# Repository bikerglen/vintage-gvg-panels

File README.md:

# vintage-gvg-panels
# kalypso, series 300

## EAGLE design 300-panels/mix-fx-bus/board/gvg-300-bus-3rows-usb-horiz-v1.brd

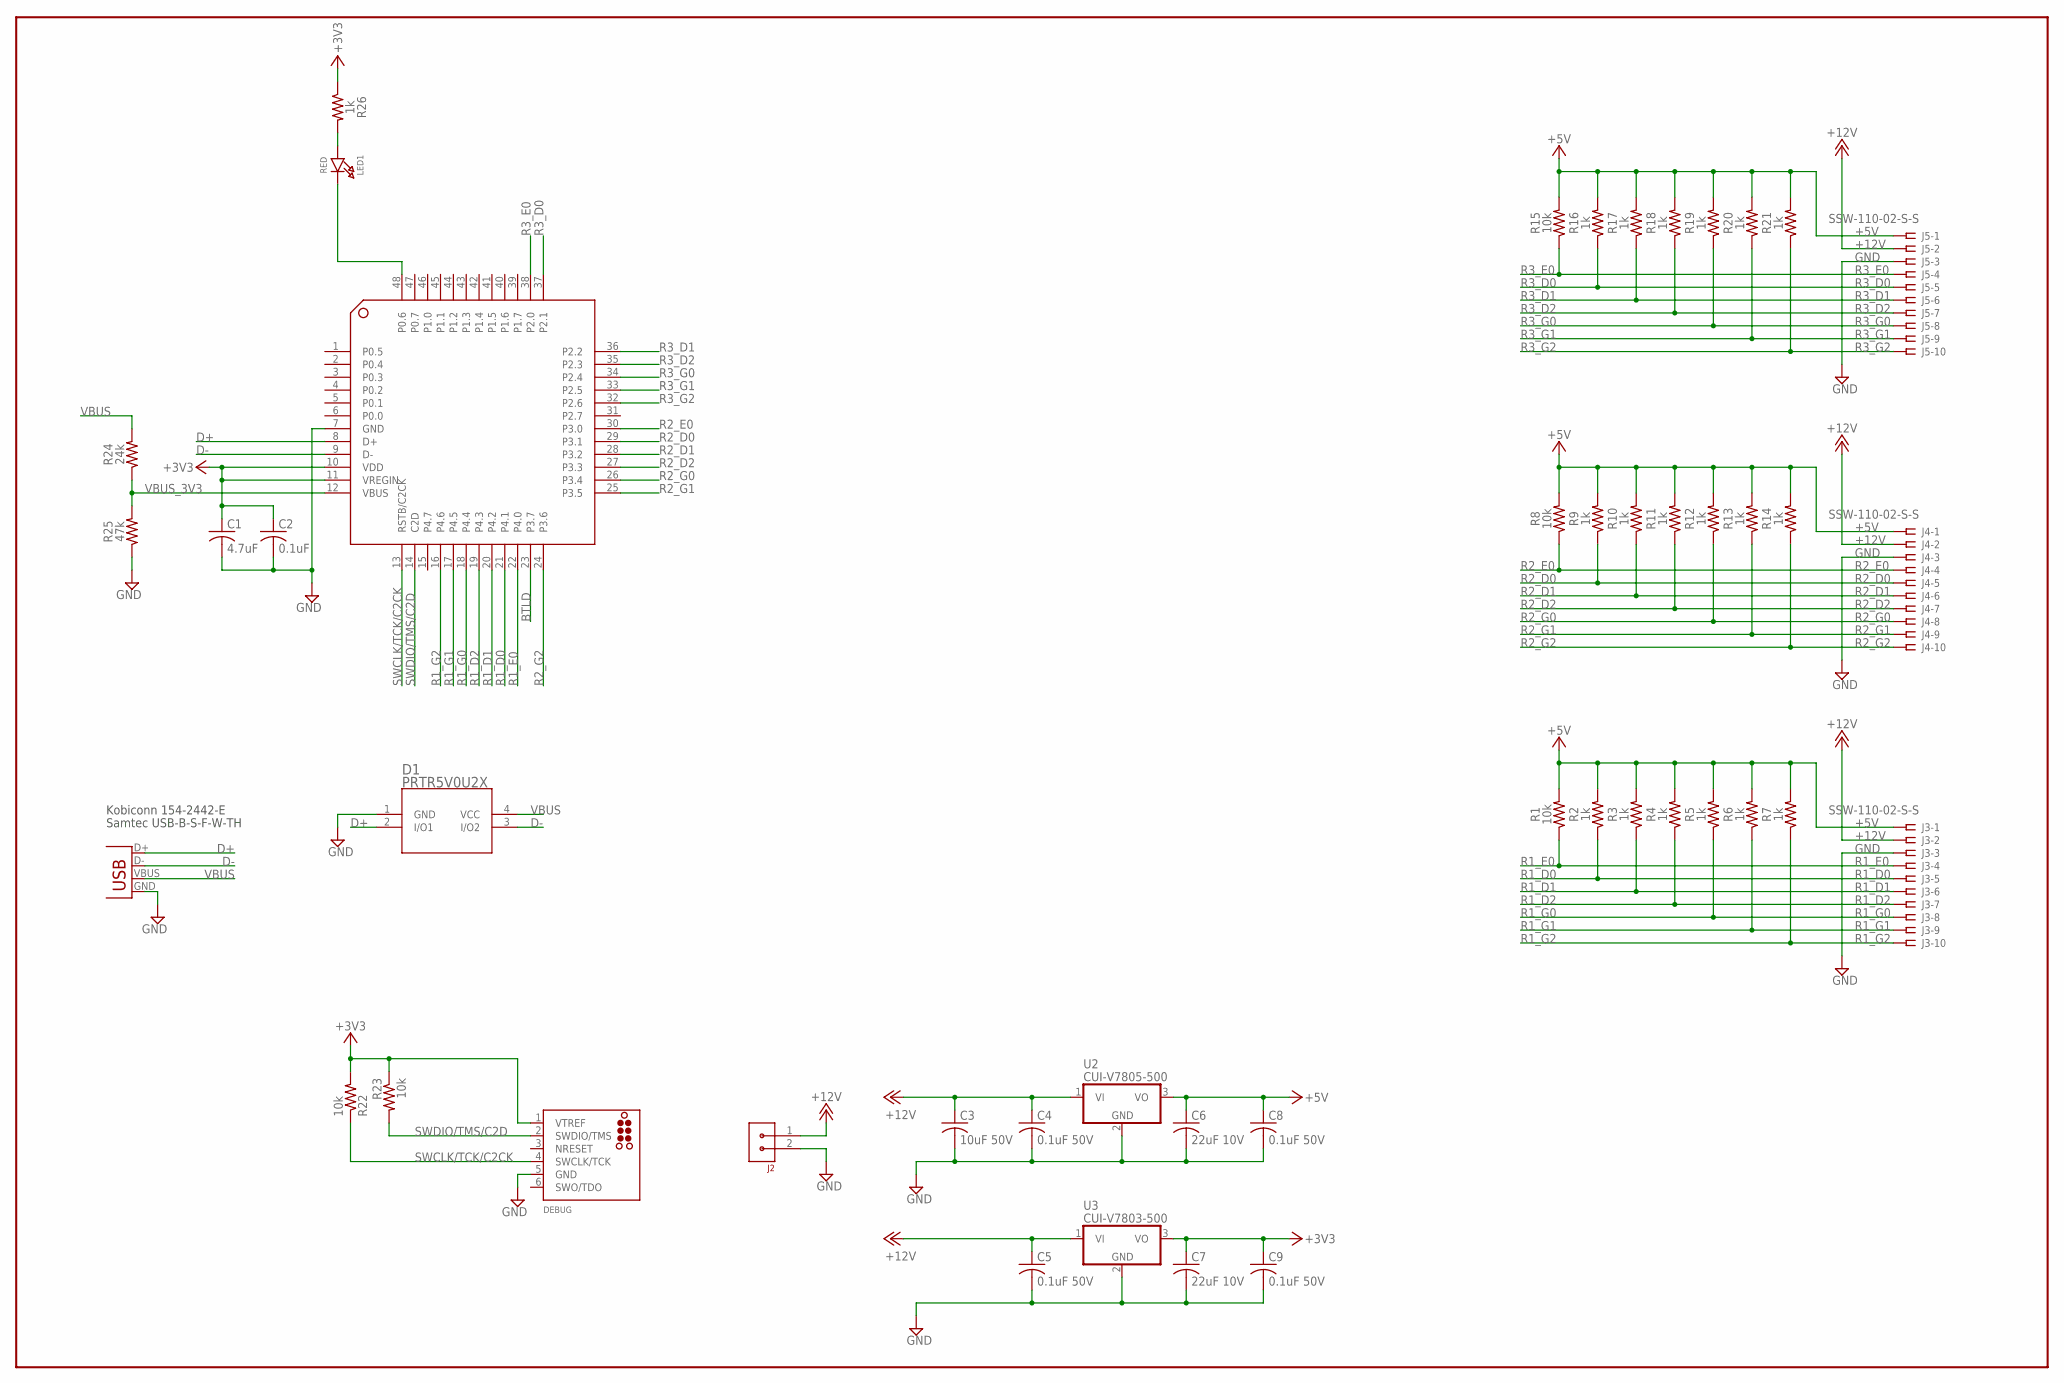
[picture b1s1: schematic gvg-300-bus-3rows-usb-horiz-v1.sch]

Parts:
C1: 4.7uF; C0805K
C2: 0.1uF; C0603K
C3: 10uF 50V; C1210K; MFR_PART_NO C1210C106K5RACTU
C4, C5, C8, C9: 0.1uF 50V; C1206K; MFR_PART_NO C1206S104M5RACTU
C6, C7: 22uF 10V; C1206K; MFR_PART_NO C1206C226K8RAC7800
D1: PRTR5V0U2X; SOT143B
DEBUG: TC2030-CTX-SWD; TC2030-MCP-NL
J1: USB-B; USB-B-PTH; MFR_PART_NO 154-2442-E
J2: CON-3.81MM-1X2-PHOENIX; CON-PHOENIX-3.81-1X2-RA
J3, J4, J5: SSW-110-02-S-S
LED1: RED; CHIPLED_0805_NOOUTLINE
R1, R8, R15, R22, R23: 10k; R0603
R2, R3, R4, R5, R6, R7, R9, R10, R11, R12, R13, R14, R16, R17, R18, R19, R20, R21, R26: 1k; R0603
R24: 24k; R0603
R25: 47k; R0603
U1: EFM8UB20F64G-B-QFP48; EFM8UB2-QFP48
U2: CUI-V7805-500; CUI-78XX-500
U3: CUI-V7803-500; CUI-78XX-500

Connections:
+3V3: C1.1, C2.1, C7.1, C9.1, DEBUG.1 (VTREF), R22.2, R23.1, R26.1, U1.10 (VDD), U1.11 (VREGIN), U3.3 (VO)
+5V: C6.1, C8.1, J3.1, J4.1, J5.1, R1.2, R2.2, R3.2, R4.2, R5.2, R6.2, R7.2, R8.2, R9.2, R10.2, R11.2, R12.2, R13.2, R14.2, R15.2, R16.2, R17.2, R18.2, R19.2, R20.2, R21.2, U2.3 (VO)
+12V: C3.1, C4.1, C5.1, J2.1, J3.2, J4.2, J5.2, U2.1 (VI), U3.1 (VI)
BTLD: U1.23 (P3.7)
D+: D1.2 (I/O1), J1.D+, U1.8 (D+)
D-: D1.3 (I/O2), J1.D-, U1.9 (D-)
GND: C1.2, C2.2, C3.2, C4.2, C5.2, C6.2, C7.2, C8.2, C9.2, D1.1 (GND), DEBUG.5 (GND), J1.GND, J2.2, J3.3, J4.3, J5.3, R25.1, U1.7 (GND), U2.2 (GND), U3.2 (GND)
unnamed: LED1.A, R26.2
unnamed: LED1.C, U1.48 (P0.6)
NRESET: DEBUG.3 (NRESET)
R1_D0: J3.5, R2.1, U1.21 (P4.1)
R1_D1: J3.6, R3.1, U1.20 (P4.2)
R1_D2: J3.7, R4.1, U1.19 (P4.3)
R1_E0: J3.4, R1.1, U1.22 (P4.0)
R1_G0: J3.8, R5.1, U1.18 (P4.4)
R1_G1: J3.9, R6.1, U1.17 (P4.5)
R1_G2: J3.10, R7.1, U1.16 (P4.6)
R2_D0: J4.5, R9.1, U1.29 (P3.1)
R2_D1: J4.6, R10.1, U1.28 (P3.2)
R2_D2: J4.7, R11.1, U1.27 (P3.3)
R2_E0: J4.4, R8.1, U1.30 (P3.0)
R2_G0: J4.8, R12.1, U1.26 (P3.4)
R2_G1: J4.9, R13.1, U1.25 (P3.5)
R2_G2: J4.10, R14.1, U1.24 (P3.6)
R3_D0: J5.5, R16.1, U1.37 (P2.1)
R3_D1: J5.6, R17.1, U1.36 (P2.2)
R3_D2: J5.7, R18.1, U1.35 (P2.3)
R3_E0: J5.4, R15.1, U1.38 (P2.0)
R3_G0: J5.8, R19.1, U1.34 (P2.4)
R3_G1: J5.9, R20.1, U1.33 (P2.5)
R3_G2: J5.10, R21.1, U1.32 (P2.6)
SWCLK/TCK/C2CK: DEBUG.4 (SWCLK/TCK), R22.1, U1.13 (RSTB/C2CK)
SWDIO/TMS/C2D: DEBUG.2 (SWDIO/TMS), R23.2, U1.14 (C2D)
VBUS: D1.4 (VCC), J1.VBUS, R24.2
VBUS_3V3: R24.1, R25.2, U1.12 (VBUS)

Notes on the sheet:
Kobiconn 154-2442-E
Samtec USB-B-S-F-W-TH

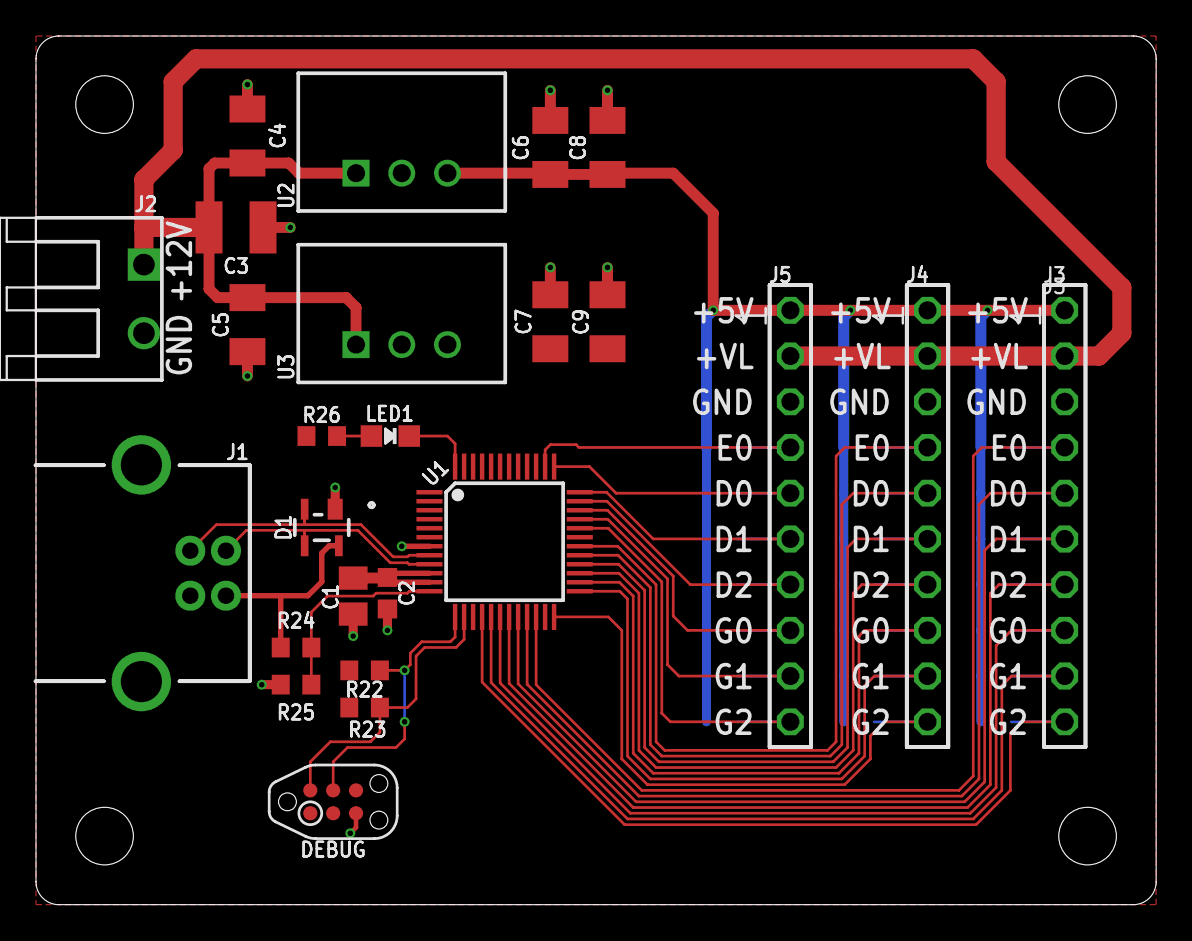
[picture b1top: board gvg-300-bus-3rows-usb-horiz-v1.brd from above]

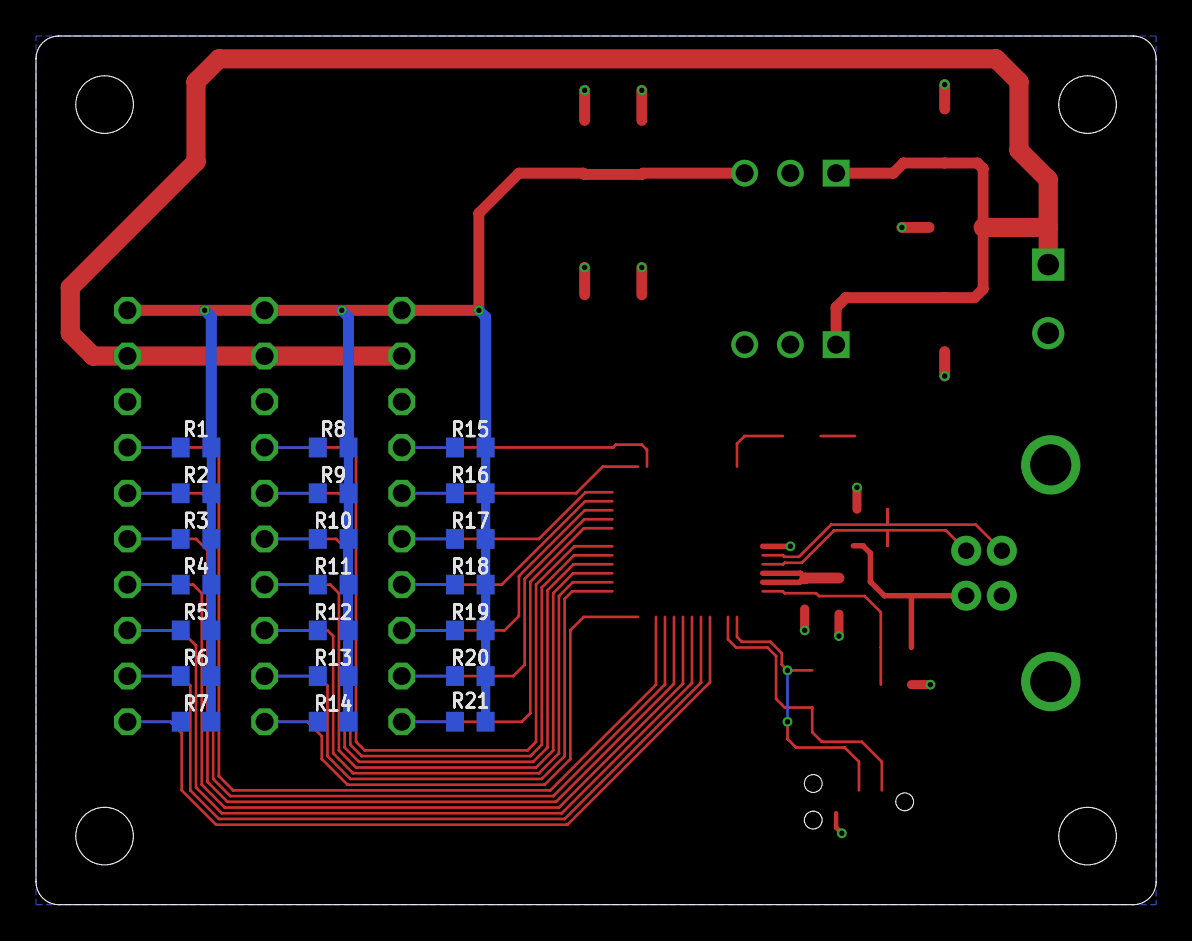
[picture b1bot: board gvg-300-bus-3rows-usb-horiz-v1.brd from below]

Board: 2 copper layers, 62.2 x 48.3 mm, 46 parts (21 on the bottom side), 33 nets.

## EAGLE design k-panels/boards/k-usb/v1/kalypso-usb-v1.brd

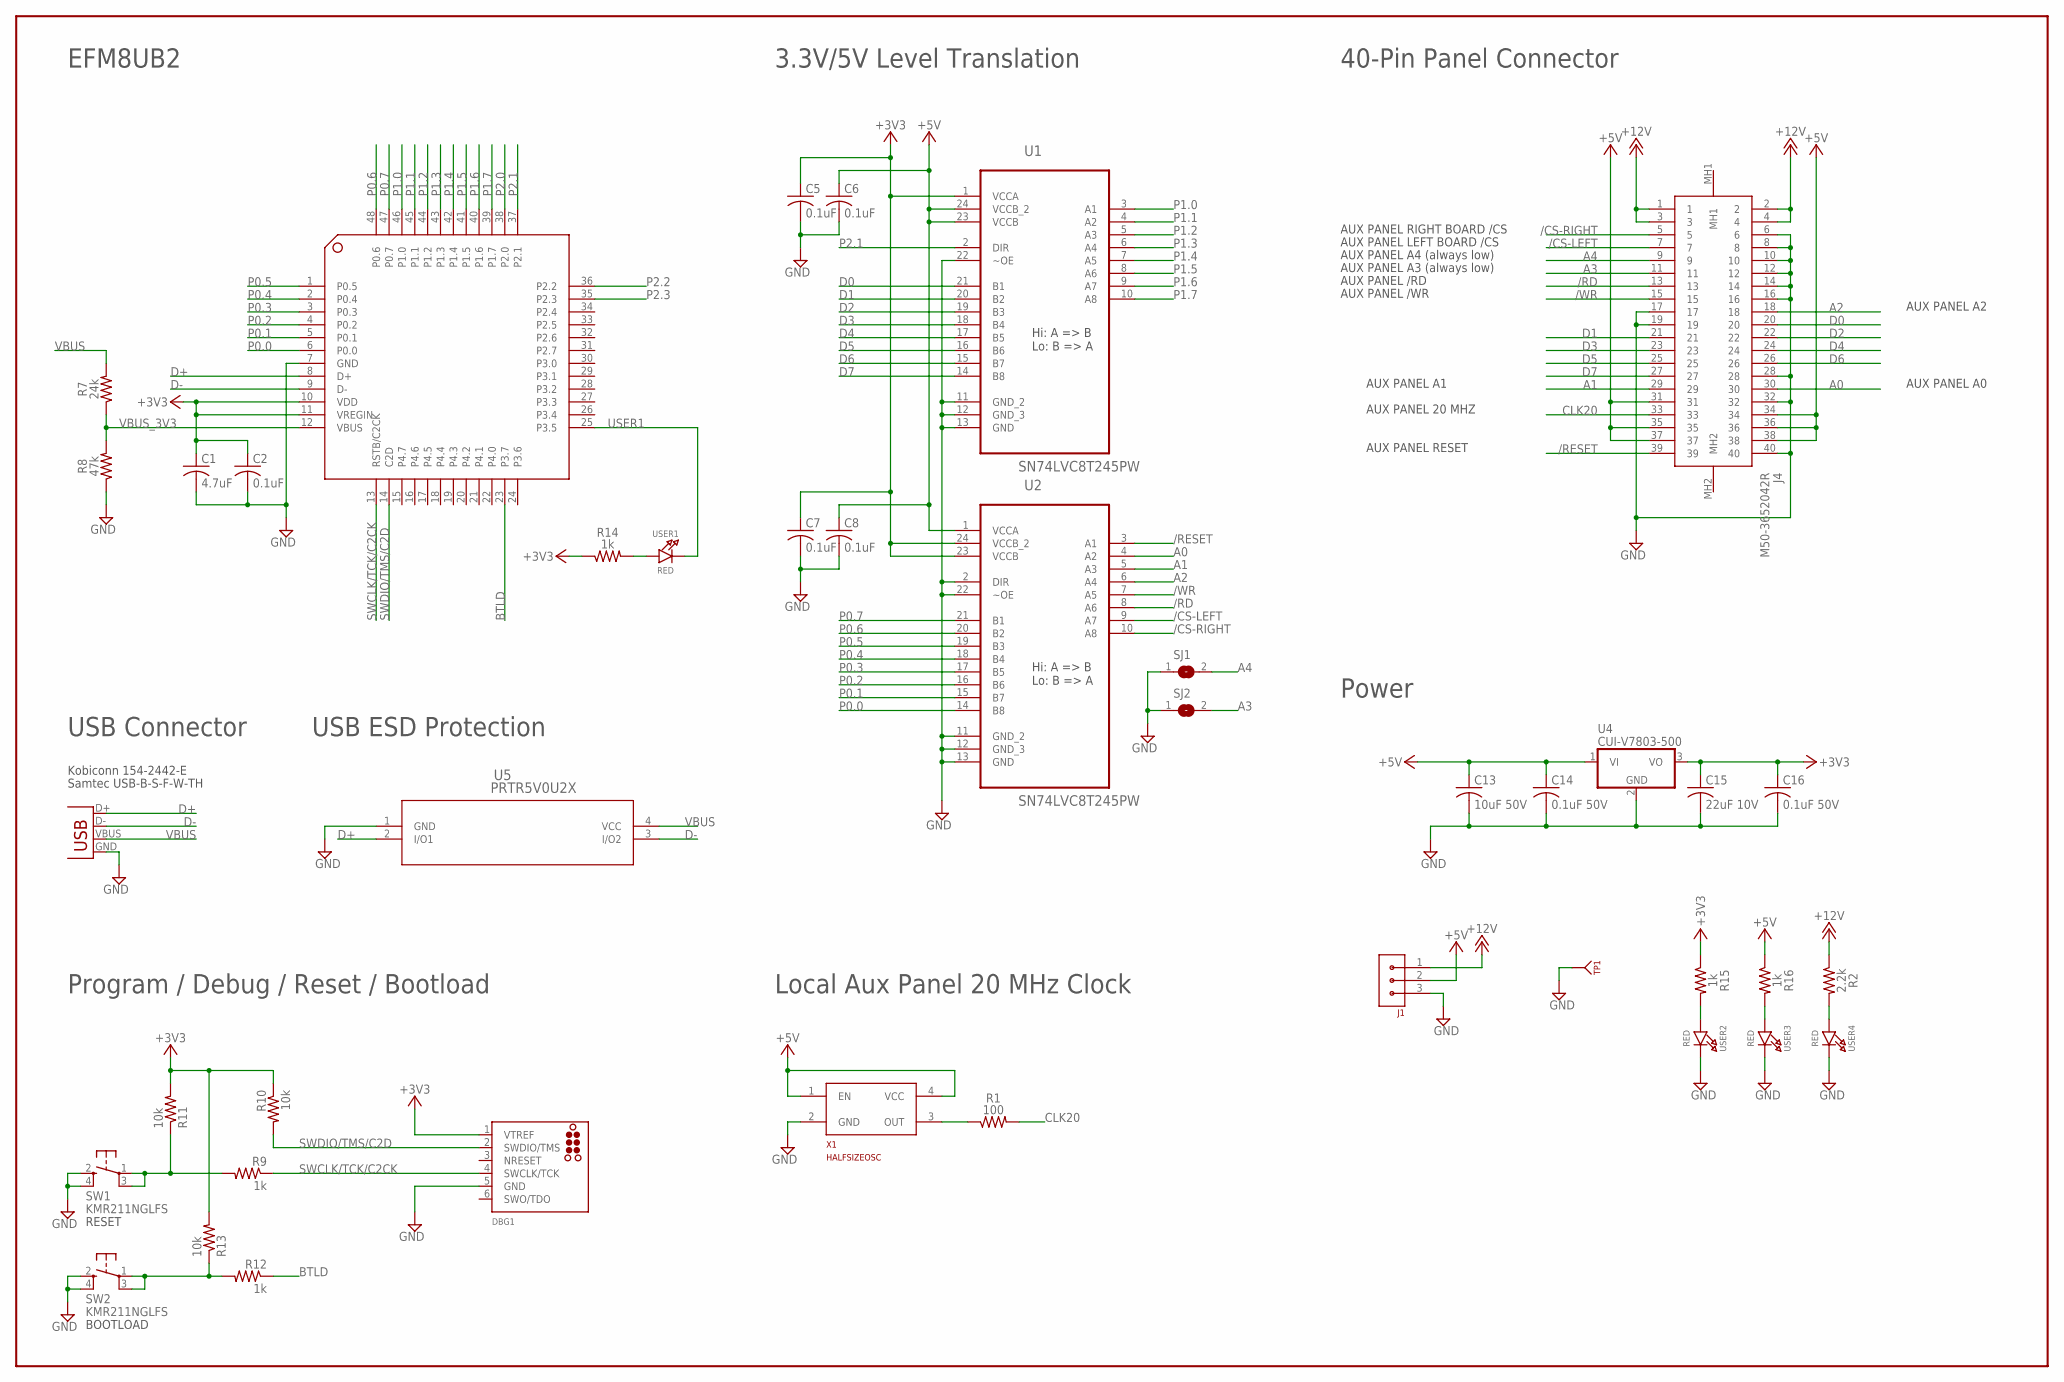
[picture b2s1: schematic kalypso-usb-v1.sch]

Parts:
C1: 4.7uF; C0805K
C2, C5, C6, C7, C8: 0.1uF; C0603K
C13: 10uF 50V; C1210K; MFR_PART_NO C1210C106K5RACTU
C14, C16: 0.1uF 50V; C1206K; MFR_PART_NO C1206S104M5RACTU
C15: 22uF 10V; C1206K; MFR_PART_NO C1206C226K8RAC7800
DBG1: TC2030-CTX-SWD; TC2030-MCP-NL
J1: CON-3.81MM-1X3-PHOENIX-RA; CON-PHOENIX-3.81-1X3-RA
J2: USB-B; USB-B-PTH; MFR_PART_NO 154-2442-E
J4: M50-3652042R; M503652042R
R1: 100; R0603
R2: 2.2k; R0603
R7: 24k; R0603
R8: 47k; R0603
R9, R12, R14, R15, R16: 1k; R0603
R10, R11, R13: 10k; R0603
SJ1, SJ2: SJ
SW1, SW2: KMR211NGLFS; KMR2
TP1: KEYSTONE_500X; KEYSTONE_TP500X
U1, U2: SN74LVC8T245PW; SOP65P640X120-24N
U4: CUI-V7803-500; CUI-78XX-500
U5: PRTR5V0U2X; SOT143B
U6: EFM8UB20F64G-B-QFP48; EFM8UB2-QFP48
USER1, USER2, USER3, USER4: RED; CHIPLED_0805_NOOUTLINE
X1: HALFSIZEOSC

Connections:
+3V3: C1.1, C2.1, C5.1, C7.1, C15.1, C16.1, DBG1.1 (VTREF), R10.1, R11.2, R13.2, R14.1, R15.1, U1.1 (VCCA), U2.23 (VCCB), U2.24 (VCCB_2), U4.3 (VO), U6.10 (VDD), U6.11 (VREGIN)
+5V: C6.1, C8.1, C13.1, C14.1, J1.2, J4.31, J4.34, J4.35, J4.36, J4.37, J4.38, R16.1, U1.23 (VCCB), U1.24 (VCCB_2), U2.1 (VCCA), U4.1 (VI), X1.1 (EN), X1.4 (VCC)
+12V: J1.1, J4.1, J4.2, J4.3, J4.4, R2.1
/CS-LEFT: J4.7, U2.9 (A7)
/CS-RIGHT: J4.5, U2.10 (A8)
/RD: J4.13, U2.8 (A6)
/RESET: J4.39, U2.3 (A1)
/WR: J4.15, U2.7 (A5)
A0: J4.30, U2.4 (A2)
A1: J4.29, U2.5 (A3)
A2: J4.18, U2.6 (A4)
A3: J4.11, SJ2.2
A4: J4.9, SJ1.2
BTLD: R12.1, U6.23 (P3.7)
CLK20: J4.33, R1.2
D0: J4.20, U1.21 (B1)
D1: J4.21, U1.20 (B2)
D2: J4.22, U1.19 (B3)
D3: J4.23, U1.18 (B4)
D4: J4.24, U1.17 (B5)
D5: J4.25, U1.16 (B6)
D6: J4.26, U1.15 (B7)
D7: J4.27, U1.14 (B8)
D+: J2.D+, U5.2 (I/O1), U6.8 (D+)
D-: J2.D-, U5.3 (I/O2), U6.9 (D-)
GND: C1.2, C2.2, C5.2, C6.2, C7.2, C8.2, C13.2, C14.2, C15.2, C16.2, DBG1.5 (GND), J1.3, J2.GND, J4.6, J4.8, J4.10, J4.12, J4.14, J4.16, J4.17, J4.19, J4.28, J4.32, J4.40, R8.1, SJ1.1, SJ2.1, SW1.2 (S), SW1.4 (S1), SW2.2 (S), SW2.4 (S1), TP1.1, U1.11 (GND_2), U1.12 (GND_3), U1.13 (GND), U1.22 (~OE), U2.2 (DIR), U2.11 (GND_2), U2.12 (GND_3), U2.13 (GND), U2.22 (~OE), U4.2 (GND), U5.1 (GND), U6.7 (GND), USER2.C, USER3.C, USER4.C, X1.2 (GND)
unnamed: R1.1, X1.3 (OUT)
unnamed: R14.2, USER1.A
unnamed: R15.2, USER2.A
unnamed: R16.2, USER3.A
unnamed: R2.2, USER4.A
NRESET: DBG1.3 (NRESET)
P0.0: U2.14 (B8), U6.6 (P0.0)
P0.1: U2.15 (B7), U6.5 (P0.1)
P0.2: U2.16 (B6), U6.4 (P0.2)
P0.3: U2.17 (B5), U6.3 (P0.3)
P0.4: U2.18 (B4), U6.2 (P0.4)
P0.5: U2.19 (B3), U6.1 (P0.5)
P0.6: U2.20 (B2), U6.48 (P0.6)
P0.7: U2.21 (B1), U6.47 (P0.7)
P1.0: U1.3 (A1), U6.46 (P1.0)
P1.1: U1.4 (A2), U6.45 (P1.1)
P1.2: U1.5 (A3), U6.44 (P1.2)
P1.3: U1.6 (A4), U6.43 (P1.3)
P1.4: U1.7 (A5), U6.42 (P1.4)
P1.5: U1.8 (A6), U6.41 (P1.5)
P1.6: U1.9 (A7), U6.40 (P1.6)
P1.7: U1.10 (A8), U6.39 (P1.7)
P2.0: U6.38 (P2.0)
P2.1: U1.2 (DIR), U6.37 (P2.1)
P2.2: U6.36 (P2.2)
P2.3: U6.35 (P2.3)
SW1: R9.2, R11.1, SW1.1, SW1.3 (P1)
SW2: R12.2, R13.1, SW2.1, SW2.3 (P1)
SWCLK/TCK/C2CK: DBG1.4 (SWCLK/TCK), R9.1, U6.13 (RSTB/C2CK)
SWDIO/TMS/C2D: DBG1.2 (SWDIO/TMS), R10.2, U6.14 (C2D)
USER1: U6.25 (P3.5), USER1.C
VBUS: J2.VBUS, R7.2, U5.4 (VCC)
VBUS_3V3: R7.1, R8.2, U6.12 (VBUS)

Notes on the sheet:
RESET
BOOTLOAD
Kobiconn 154-2442-E
Samtec USB-B-S-F-W-TH
USB ESD Protection
Hi: A => B Lo: B => A
AUX PANEL 20 MHZ
AUX PANEL RIGHT BOARD /CS
AUX PANEL /RD
AUX PANEL /WR
AUX PANEL LEFT BOARD /CS
AUX PANEL RESET
AUX PANEL A0
AUX PANEL A2
AUX PANEL A1
AUX PANEL A3 (always low)
AUX PANEL A4 (always low)
USB Connector
Program / Debug / Reset / Bootload
EFM8UB2
3.3V/5V Level Translation
Power
40-Pin Panel Connector
Local Aux Panel 20 MHz Clock

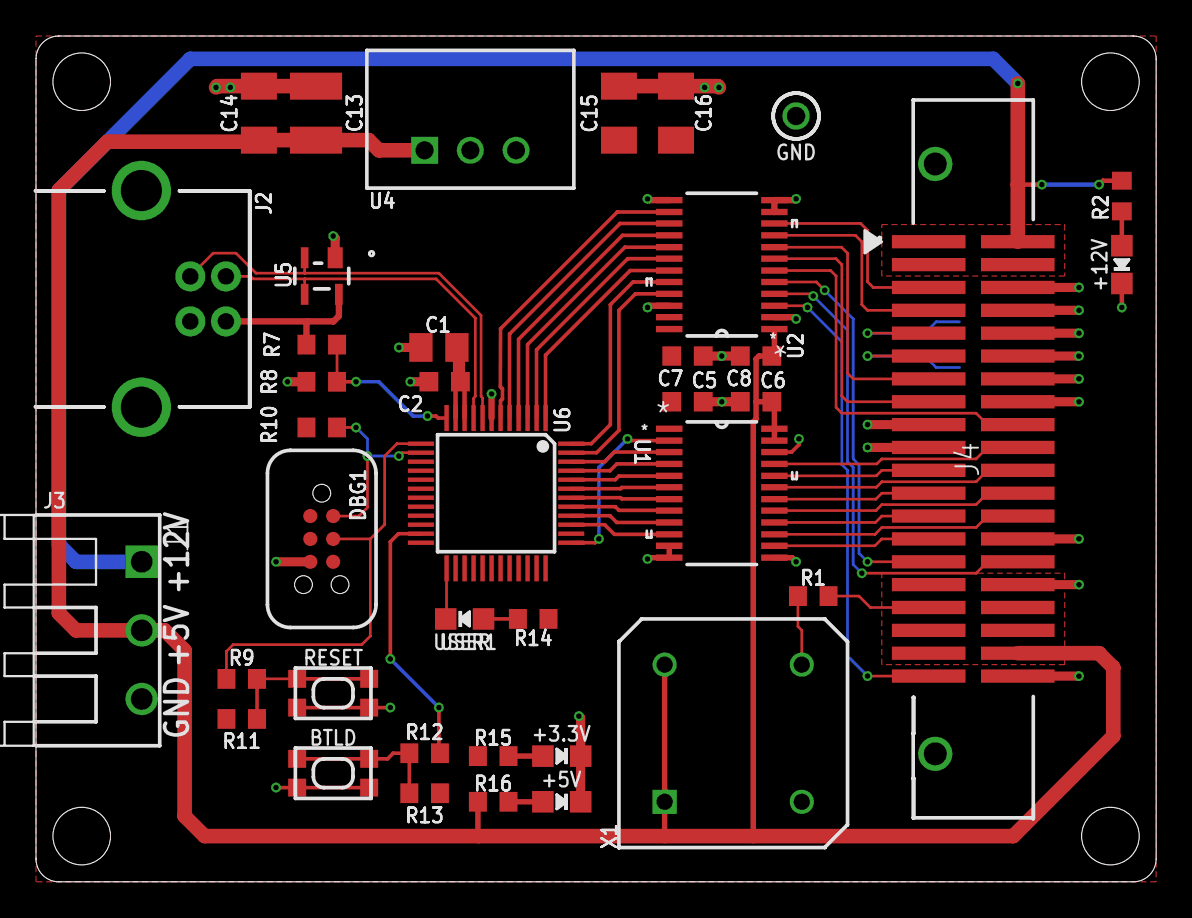
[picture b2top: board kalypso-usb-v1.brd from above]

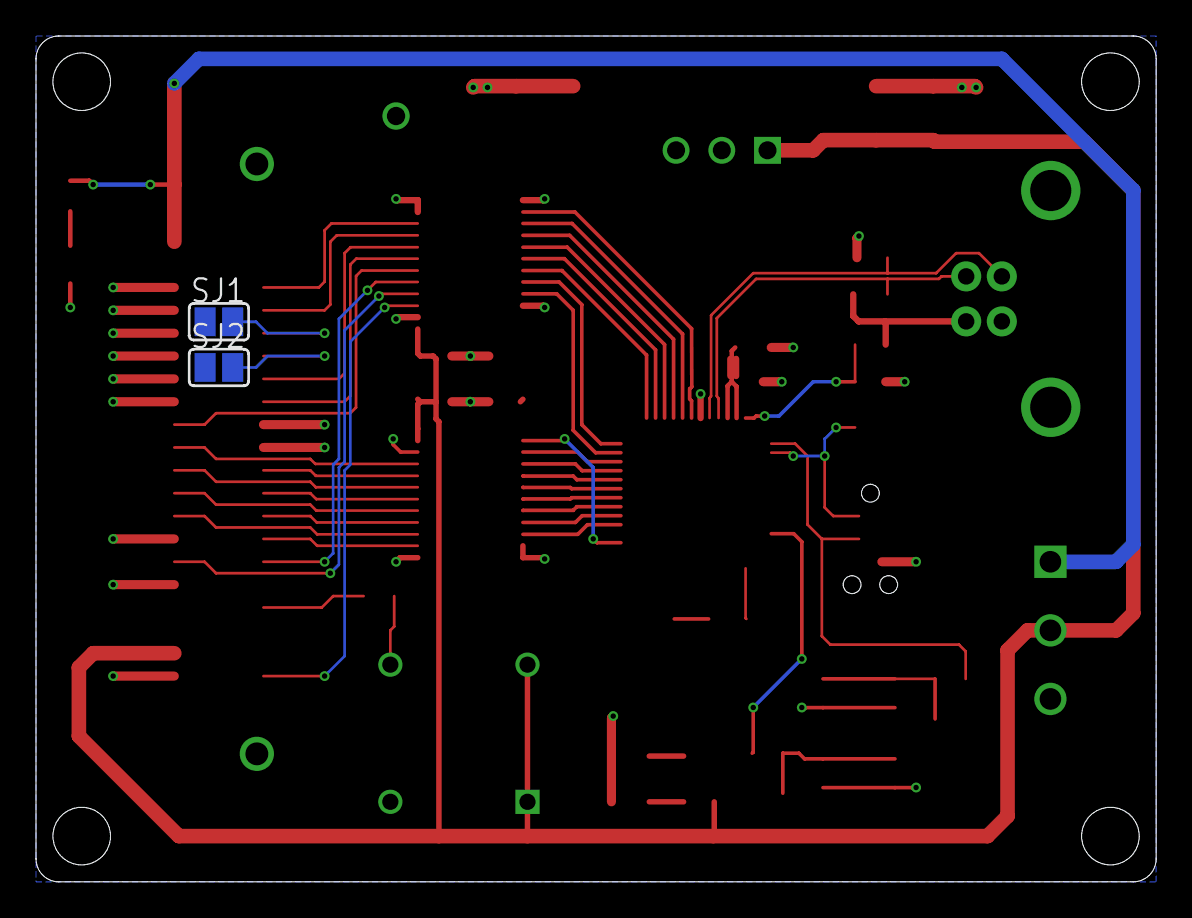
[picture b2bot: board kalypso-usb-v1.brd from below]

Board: 2 copper layers, 62.2 x 47.0 mm, 41 parts (2 on the bottom side), 55 nets.

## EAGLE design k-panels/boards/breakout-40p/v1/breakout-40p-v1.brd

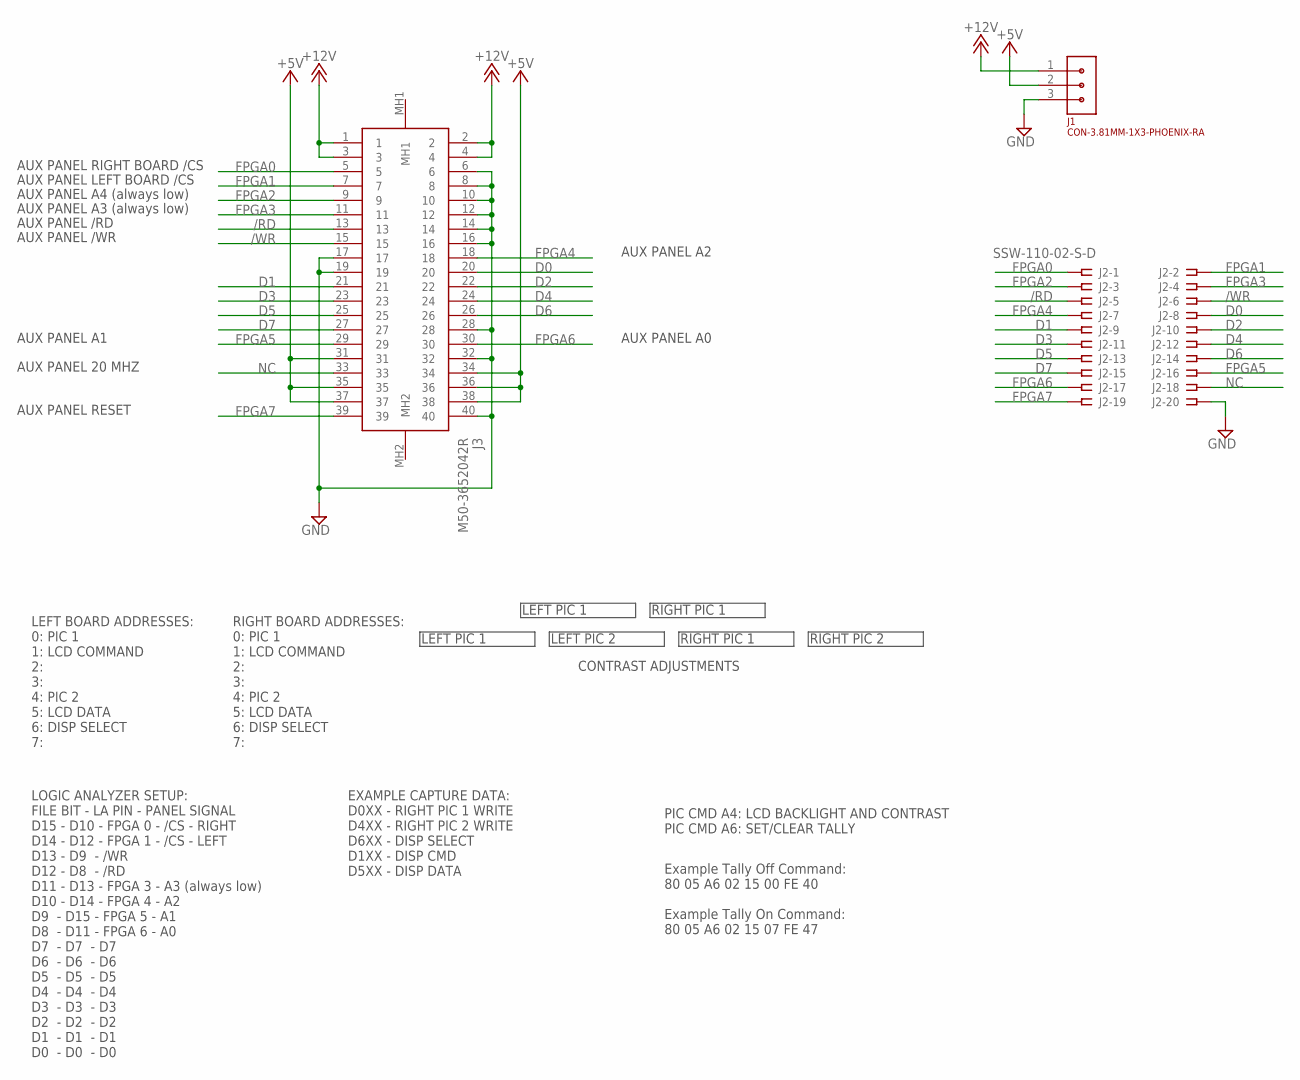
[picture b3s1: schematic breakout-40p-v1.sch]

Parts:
J1: CON-3.81MM-1X3-PHOENIX-RA; CON-PHOENIX-3.81-1X3-RA
J2: SSW-110-02-S-D
J3: M50-3652042R; M503652042R

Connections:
+5V: J1.2, J3.31, J3.34, J3.35, J3.36, J3.37, J3.38
+12V: J1.1, J3.1, J3.2, J3.3, J3.4
/RD: J2.5, J3.13
/WR: J2.6, J3.15
D0: J2.8, J3.20
D1: J2.9, J3.21
D2: J2.10, J3.22
D3: J2.11, J3.23
D4: J2.12, J3.24
D5: J2.13, J3.25
D6: J2.14, J3.26
D7: J2.15, J3.27
FPGA0: J2.1, J3.5
FPGA1: J2.2, J3.7
FPGA2: J2.3, J3.9
FPGA3: J2.4, J3.11
FPGA4: J2.7, J3.18
FPGA5: J2.16, J3.29
FPGA6: J2.17, J3.30
FPGA7: J2.19, J3.39
GND: J1.3, J2.20, J3.6, J3.8, J3.10, J3.12, J3.14, J3.16, J3.17, J3.19, J3.28, J3.32, J3.40
NC: J2.18, J3.33

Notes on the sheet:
AUX PANEL 20 MHZ
AUX PANEL RIGHT BOARD /CS
AUX PANEL /RD
AUX PANEL /WR
AUX PANEL LEFT BOARD /CS
AUX PANEL RESET
AUX PANEL A0
AUX PANEL A2
AUX PANEL A1
LEFT BOARD ADDRESSES: 0: PIC 1 1: LCD COMMAND 2: 3: 4: PIC 2 5: LCD DATA 6: DISP SELECT 7:
RIGHT BOARD ADDRESSES: 0: PIC 1 1: LCD COMMAND 2: 3: 4: PIC 2 5: LCD DATA 6: DISP SELECT 7:
LEFT PIC 1
LEFT PIC 2
RIGHT PIC 2
CONTRAST ADJUSTMENTS
AUX PANEL A3 (always low)
AUX PANEL A4 (always low)
RIGHT PIC 1
EXAMPLE CAPTURE DATA: D0XX - RIGHT PIC 1 WRITE D4XX - RIGHT PIC 2 WRITE D6XX - DISP SELECT D1XX - DISP CMD D5XX - DISP DATA
LOGIC ANALYZER SETUP: FILE BIT - LA PIN - PANEL SIGNAL D15 - D10 - FPGA 0 - /CS - RIGHT D14 - D12 - FPGA 1 - /CS - LEFT D13 - D9 - /WR D12 - D8 - /RD D11 - D13 - FPGA 3 - A3 (always low) D10 - D14 - FPGA 4 - A2 D9 - D15 - FPGA 5 - A1 D8 - D11 - FPGA 6 - A0 D7 - D7 - D7 D6 - D6 - D6 D5 - D5 - D5 D4 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
PIC CMD A4: LCD BACKLIGHT AND CONTRAST PIC CMD A6: SET/CLEAR TALLY
Example Tally Off Command: 80 05 A6 02 15 00 FE 40 Example Tally On Command: 80 05 A6 02 15 07 FE 47

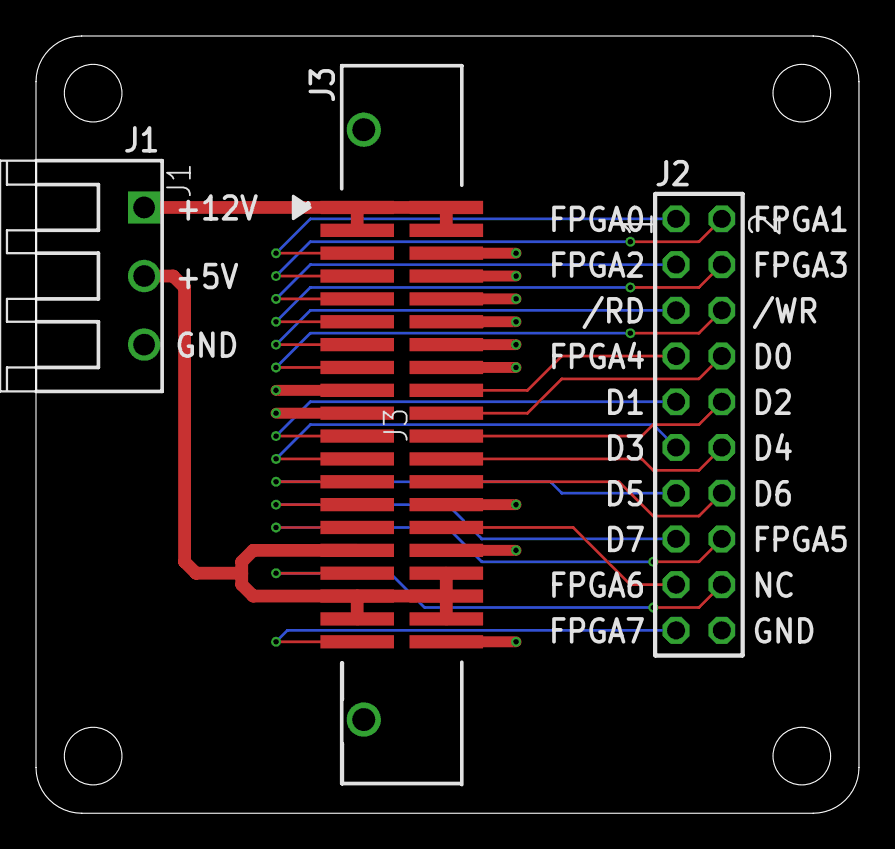
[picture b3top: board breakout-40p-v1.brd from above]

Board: 2 copper layers, 45.7 x 43.2 mm, 3 parts (0 on the bottom side), 22 nets.

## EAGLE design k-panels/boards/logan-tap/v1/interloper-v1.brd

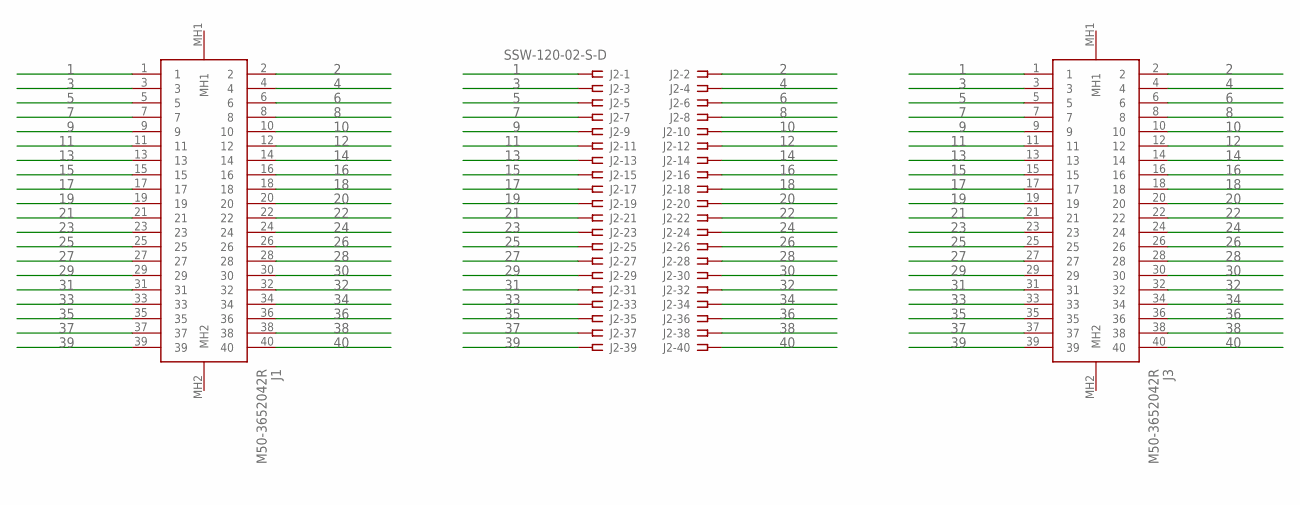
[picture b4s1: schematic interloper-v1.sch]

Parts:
J1, J3: M50-3652042R; M503652042R
J2: SSW-120-02-S-D

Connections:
1: J1.1, J2.1, J3.1
2: J1.2, J2.2, J3.2
3: J1.3, J2.3, J3.3
4: J1.4, J2.4, J3.4
5: J1.5, J2.5, J3.5
6: J1.6, J2.6, J3.6
7: J1.7, J2.7, J3.7
8: J1.8, J2.8, J3.8
9: J1.9, J2.9, J3.9
10: J1.10, J2.10, J3.10
11: J1.11, J2.11, J3.11
12: J1.12, J2.12, J3.12
13: J1.13, J2.13, J3.13
14: J1.14, J2.14, J3.14
15: J1.15, J2.15, J3.15
16: J1.16, J2.16, J3.16
17: J1.17, J2.17, J3.17
18: J1.18, J2.18, J3.18
19: J1.19, J2.19, J3.19
20: J1.20, J2.20, J3.20
21: J1.21, J2.21, J3.21
22: J1.22, J2.22, J3.22
23: J1.23, J2.23, J3.23
24: J1.24, J2.24, J3.24
25: J1.25, J2.25, J3.25
26: J1.26, J2.26, J3.26
27: J1.27, J2.27, J3.27
28: J1.28, J2.28, J3.28
29: J1.29, J2.29, J3.29
30: J1.30, J2.30, J3.30
31: J1.31, J2.31, J3.31
32: J1.32, J2.32, J3.32
33: J1.33, J2.33, J3.33
34: J1.34, J2.34, J3.34
35: J1.35, J2.35, J3.35
36: J1.36, J2.36, J3.36
37: J1.37, J2.37, J3.37
38: J1.38, J2.38, J3.38
39: J1.39, J2.39, J3.39
40: J1.40, J2.40, J3.40

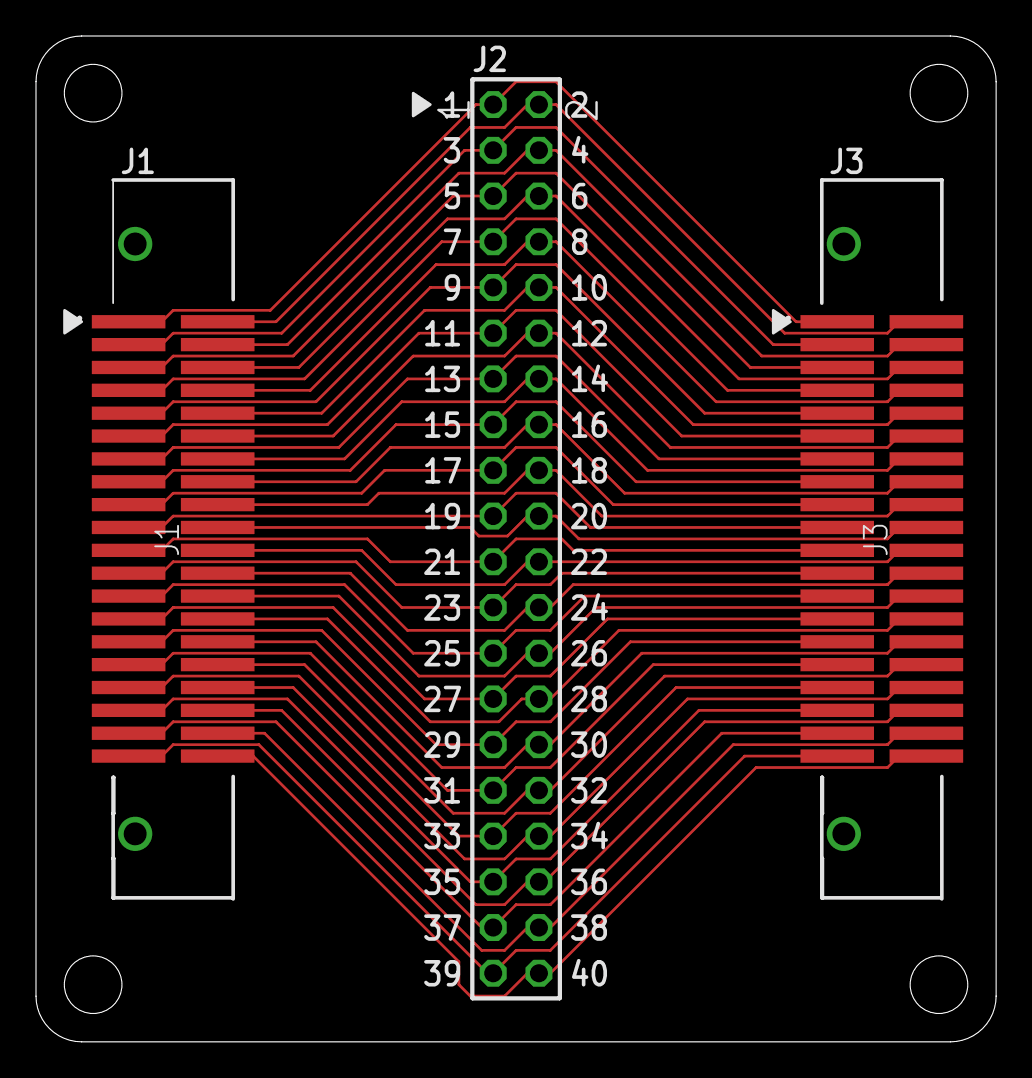
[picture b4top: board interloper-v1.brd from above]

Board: 2 copper layers, 53.3 x 55.9 mm, 3 parts (0 on the bottom side), 40 nets.

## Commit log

2020-11-26 initial checkin
2020-11-27 add attribution for icons
2021-04-08 add 300 mix effects bus board files and software
2021-04-08 auth test

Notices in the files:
parts and their libraries:
tag-connect: ©2009 ROFA.cz - modified and updated by Robert Darlington ‹rdarlington@gmail.com›
SparkFun-Connectors: Licensing: Creative Commons ShareAlike 4.0 International - https://creativecommons.org/licenses/by-sa/4.0
